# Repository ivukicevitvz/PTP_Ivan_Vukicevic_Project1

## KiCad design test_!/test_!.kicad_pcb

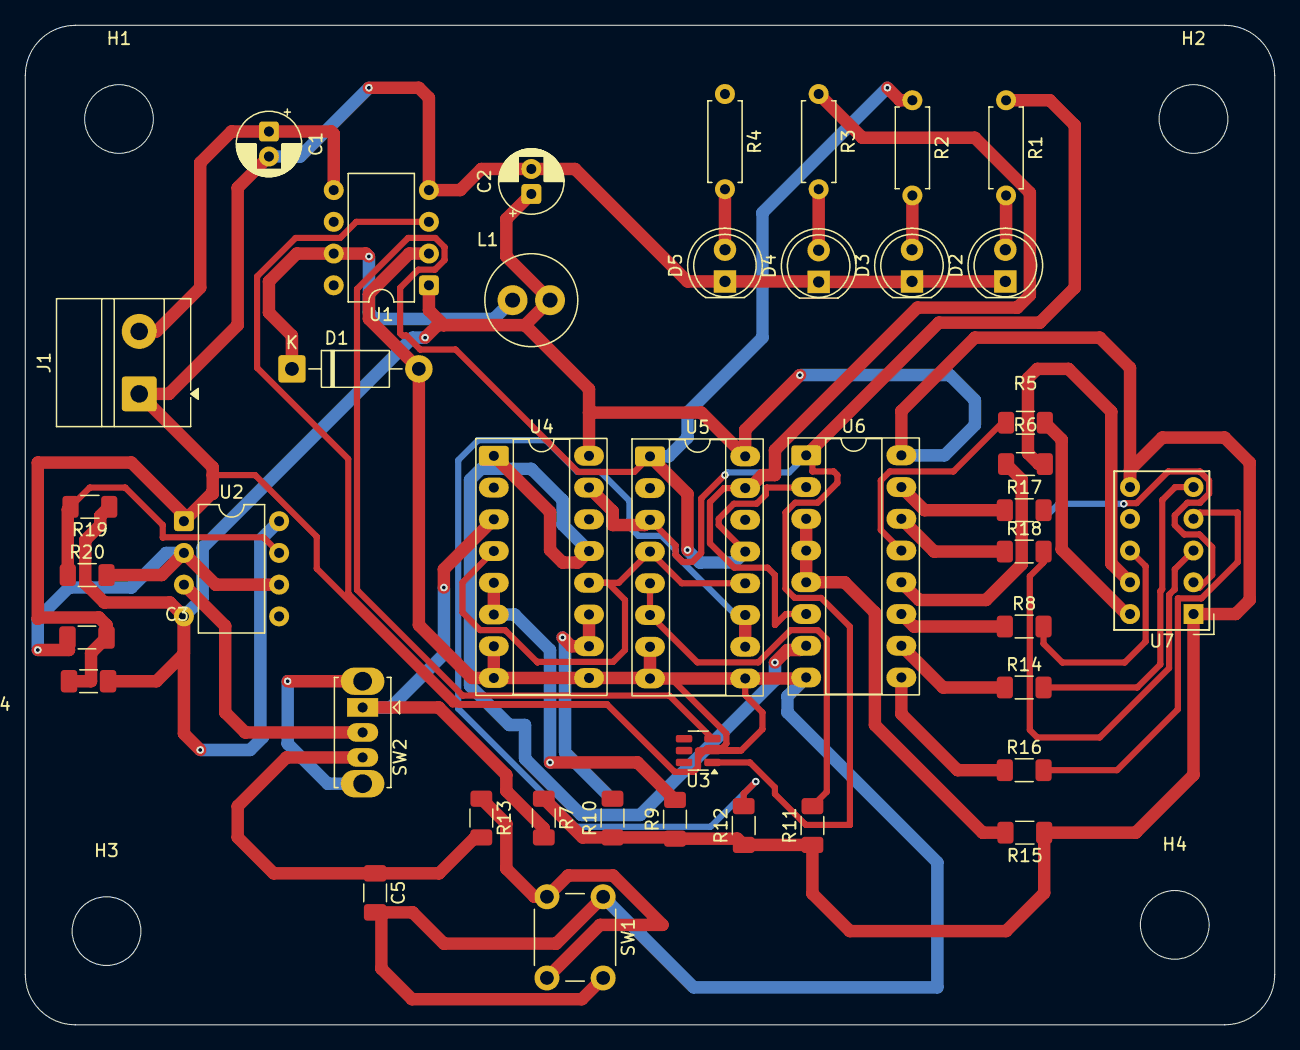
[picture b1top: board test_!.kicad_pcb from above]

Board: 2 copper layers, 100.0 x 80.0 mm, 45 parts (0 on the bottom side), 38 nets.

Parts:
C1: 22u; CP_Radial_D5.0mm_P2.00mm
C2: 220u; CP_Radial_D5.0mm_P2.00mm
C3: 10u; C_1206_3216Metric_Pad1.33x1.80mm_HandSolder
C4: 100n; C_1206_3216Metric_Pad1.33x1.80mm_HandSolder
C5: 1u; C_1206_3216Metric_Pad1.33x1.80mm_HandSolder
D1: 11DQ06; D_DO-41_SOD81_P10.16mm_Horizontal
D2, D3, D4, D5: LED; LED_D5.0mm
H1, H2, H3, H4: MountingHole; MountingHole_5.5mm
J1: Screw_Terminal_01x02; TerminalBlock_MetzConnect_Type011_RT05502HBLC_1x02_P5.00mm_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
L1: 330u; L_Radial_D7.2mm_P3.00mm_Murata_1700
R1, R2, R3, R4: 4k7; R_Axial_DIN0207_L6.3mm_D2.5mm_P7.62mm_Horizontal
R5, R6, R8, R13, R14, R16, R17, R18: 2k; R_1206_3216Metric_Pad1.30x1.75mm_HandSolder
R7, R9, R10, R11, R12, R15: 10k; R_1206_3216Metric_Pad1.30x1.75mm_HandSolder
R19, R20: 47k; R_1206_3216Metric_Pad1.30x1.75mm_HandSolder
SW1: SW_Push; SW_PUSH_6mm_H4.3mm
SW2: SW_Wuerth_450301014042; SW_Slide_SPDT_Straight_CK_OS102011MS2Q
U1: LM2574N-5; DIP-8_W7.62mm
U2: NE555P; DIP-8_W7.62mm
U3: SOT-23-6
U4, U5: 4027; DIP-16_W7.62mm_Socket_LongPads
U6: 74LS47; DIP-16_W7.62mm_Socket_LongPads
U7: HDSP-7401

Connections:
555: SW2.2 (C), U2.3 (Q)
+5V: C2.1, C4.1, L1.2, R7.1, R9.1, R10.1, R11.1, R12.1, R15.1, R19.1, U1.1 (FB), U2.4 (R), U2.8 (VCC), U4.16 (VDD), U5.16 (VDD), U6.16 (VCC), U7.1 (CA), U7.6 (CA)
Clock: R7.2, SW2.1 (B), U4.3 (C)
GND: C1.2, C2.2, C3.2, C4.2, C5.2, D1.2 (A), D2.1 (K), D3.1 (K), D4.1 (K), D5.1 (K), J1.1, SW1.1, U1.2 (SGND), U1.3 (~ON/OFF), U1.4 (PGND), U2.1 (GND), U3.2 (GND), U4.7 (S), U4.8 (VSS), U4.9 (S), U5.7 (S), U5.8 (VSS), U5.9 (S), U6.8 (GND)
unnamed: D1.1 (K), L1.1, U1.7 (OUT)
unnamed: D2.2 (A), R1.2
unnamed: D3.2 (A), R2.2
unnamed: D4.2 (A), R3.2
unnamed: D5.2 (A), R4.2
unnamed: R13.1, SW1.2
unnamed: C5.1, R13.2, SW2.3 (A)
unnamed: R19.2, R20.1, U2.7 (DIS)
unnamed: C3.1, R20.2, U2.2 (TR), U2.6 (THR)
unnamed: R9.2, U4.5 (K), U4.6 (J)
unnamed: R10.2, U4.10 (J), U4.11 (K)
unnamed: R11.2, U5.5 (K), U5.6 (J)
unnamed: R12.2, U5.10 (J), U5.11 (K)
unnamed: R15.2, U6.3 (LT), U6.4 (BI), U6.5 (RBI)
unnamed: R5.1, U6.13 (a)
unnamed: R6.1, U6.12 (b)
unnamed: R8.1, U6.11 (c)
unnamed: R14.1, U6.10 (d)
unnamed: R16.1, U6.9 (e)
unnamed: R17.1, U6.15 (f)
unnamed: R18.1, U6.14 (g)
unnamed: R5.2, U7.10 (A)
unnamed: R6.2, U7.9 (B)
unnamed: R8.2, U7.8 (C)
unnamed: R14.2, U7.5 (D)
unnamed: R16.2, U7.4 (E)
unnamed: R17.2, U7.2 (F)
unnamed: R18.2, U7.3 (G)
Q1: R1.1, U3.1 (A), U4.15 (Q), U5.3 (C), U6.1 (B)
Q2: R2.1, U3.3 (B), U5.1 (Q), U5.13 (C), U6.2 (C)
Q3: R3.1, U5.15 (Q), U6.6 (D)
QO: U4.1 (Q), U4.13 (C), U6.7 (A)
RESET: U3.4 (Y), U4.4 (R), U4.12 (R), U5.4 (R), U5.12 (R)
VDD: C1.1, J1.2, U1.5 (VIN)

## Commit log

2025-10-29 Vjezba 2
2025-11-05 saada
2025-11-12 TEST
2025-11-25 Doma
    Domaca zadaca
2025-12-03 test
    tewtw
2025-12-10 testes
    adadada
